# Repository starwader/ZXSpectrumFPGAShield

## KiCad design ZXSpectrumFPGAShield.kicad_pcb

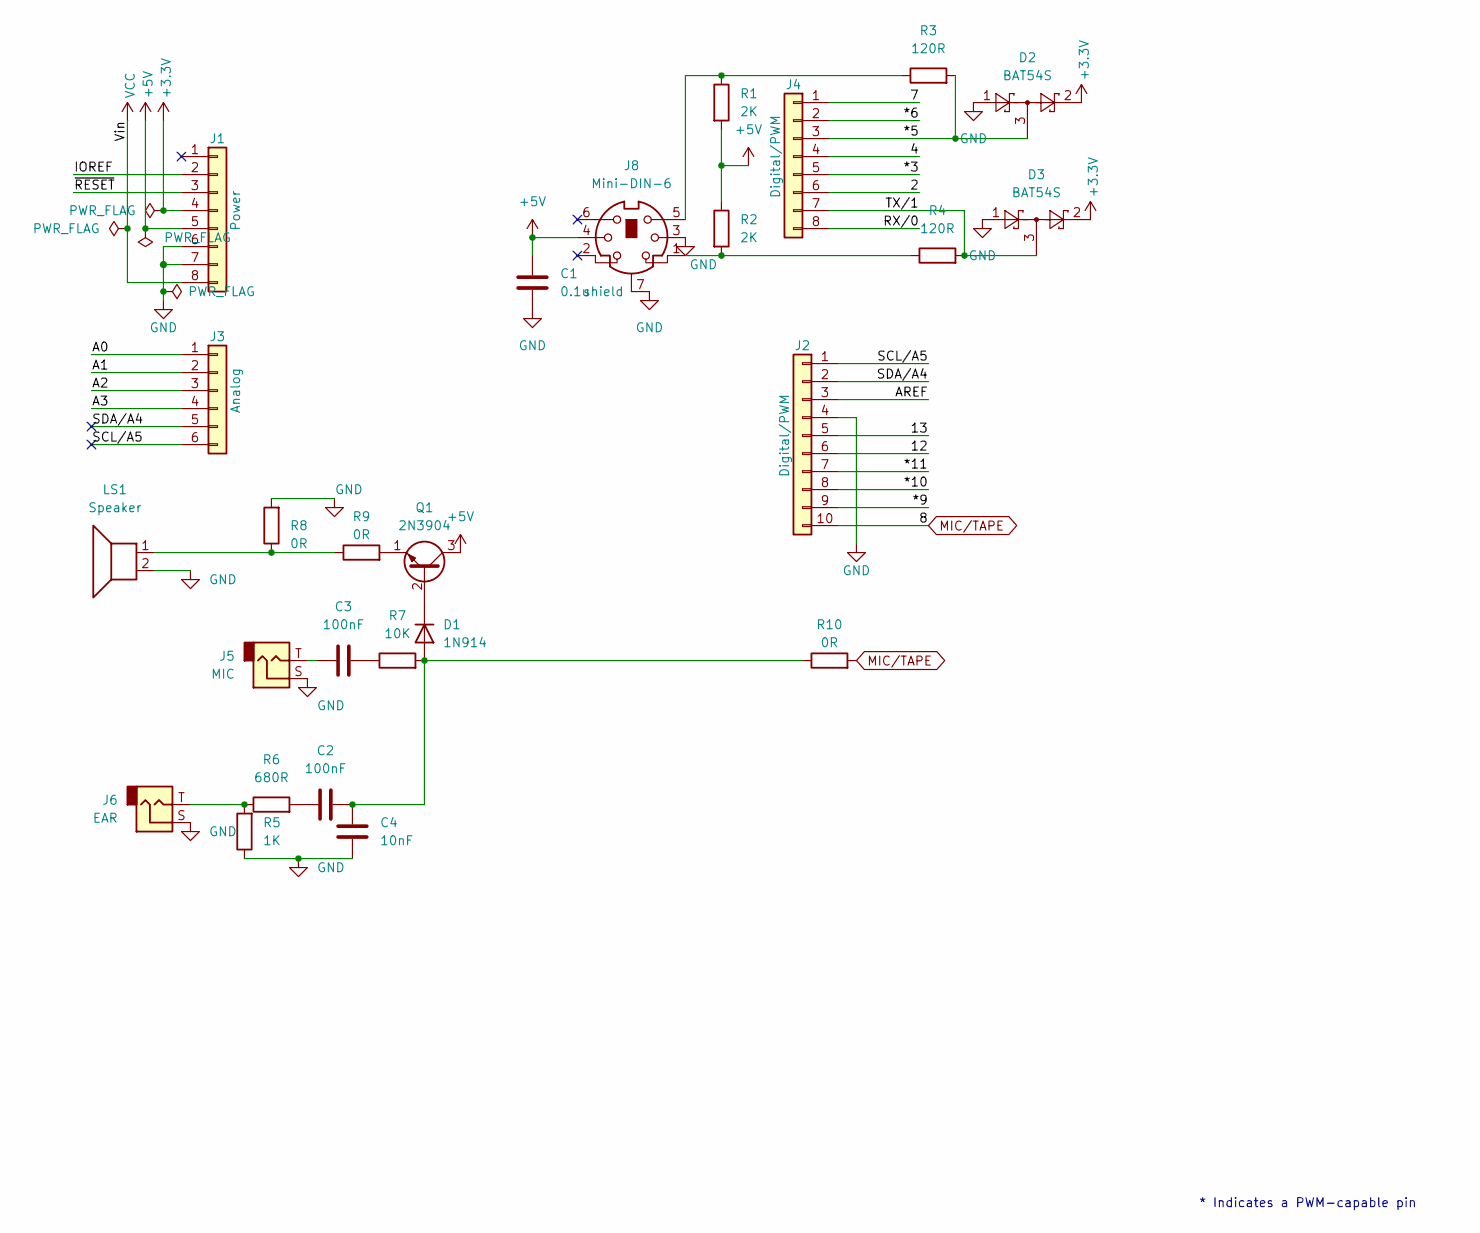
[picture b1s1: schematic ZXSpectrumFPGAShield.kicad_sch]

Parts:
C1: 0.1u; C_Axial_L3.8mm_D2.6mm_P7.50mm_Horizontal
C2, C3: 100nF; C_Rect_L7.0mm_W2.0mm_P5.00mm
C4: 10nF; C_Axial_L3.8mm_D2.6mm_P7.50mm_Horizontal
D1: 1N914; D_DO-35_SOD27_P7.62mm_Horizontal
D2, D3: BAT54S; SOT-23_Handsoldering
J1: Power; PinSocket_1x08_P2.54mm_Vertical
J2: Digital/PWM; PinSocket_1x10_P2.54mm_Vertical
J3: Analog; PinSocket_1x06_P2.54mm_Vertical
J4: Digital/PWM; PinSocket_1x08_P2.54mm_Vertical
J5: MIC; Jack_3.5mm_Lumberg_1503_07_Horizontal
J6: EAR; Jack_3.5mm_Lumberg_1503_07_Horizontal
J8: Mini-DIN-6; Connector_Mini-DIN_Female_6Pin_2rows
LS1: Speaker; Molex_KK-254_AE-6410-02A_1x02_P2.54mm_Vertical
Q1: 2N3904; TO-92_Inline
R1, R2: 2K; R_Axial_DIN0207_L6.3mm_D2.5mm_P7.62mm_Horizontal
R3, R4: 120R; R_Axial_DIN0207_L6.3mm_D2.5mm_P7.62mm_Horizontal
R5: 1K; R_Axial_DIN0207_L6.3mm_D2.5mm_P7.62mm_Horizontal
R6: 680R; R_Axial_DIN0207_L6.3mm_D2.5mm_P7.62mm_Horizontal
R7: 10K; R_Axial_DIN0207_L6.3mm_D2.5mm_P7.62mm_Horizontal
R8, R9, R10: 0R; R_Axial_DIN0207_L6.3mm_D2.5mm_P7.62mm_Horizontal

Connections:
+3V3: D2.2, D3.2, J1.4
+5V: C1.1, J1.5, J8.4, Q1.3 (C), R1.2, R2.1
/2: J4.6
/4: J4.4
/7: J4.1
/12: J2.6
/13: J2.5
/*3: J4.5
/*5: D2.3, J4.3, R3.2
/*6: J4.2
/*9: J2.9
/*10: J2.8
/*11: J2.7
/A0: J3.1
/A1: J3.2
/A2: J3.3
/A3: J3.4
/AREF: J2.3
/IOREF: J1.2
/RX/0: J4.8
/SCL/A5: J2.1, J3.6
/SDA/A4: J2.2, J3.5
/TX/1: D3.3, J4.7, R4.2
/~RESET: J1.3
GND: C1.2, C4.1, D2.1, D3.1, J1.6, J1.7, J2.4, J5.S, J6.S, J8.3, J8.7 (shield), LS1.2, R5.1, R8.2
MIC/TAPE: J2.10, R10.2
unnamed: C2.1, R6.2
unnamed: C2.2, C4.2, D1.2 (A), R7.2, R10.1
unnamed: C3.1, J5.T
unnamed: C3.2, R7.1
unnamed: D1.1 (K), Q1.2 (B)
unnamed: J6.T, R5.2, R6.1
unnamed: J8.1, R2.2, R4.1
unnamed: J8.5, R1.1, R3.1
unnamed: LS1.1, R8.1, R9.1
unnamed: Q1.1 (E), R9.2
VCC: J1.8

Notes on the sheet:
* Indicates a PWM-capable pin

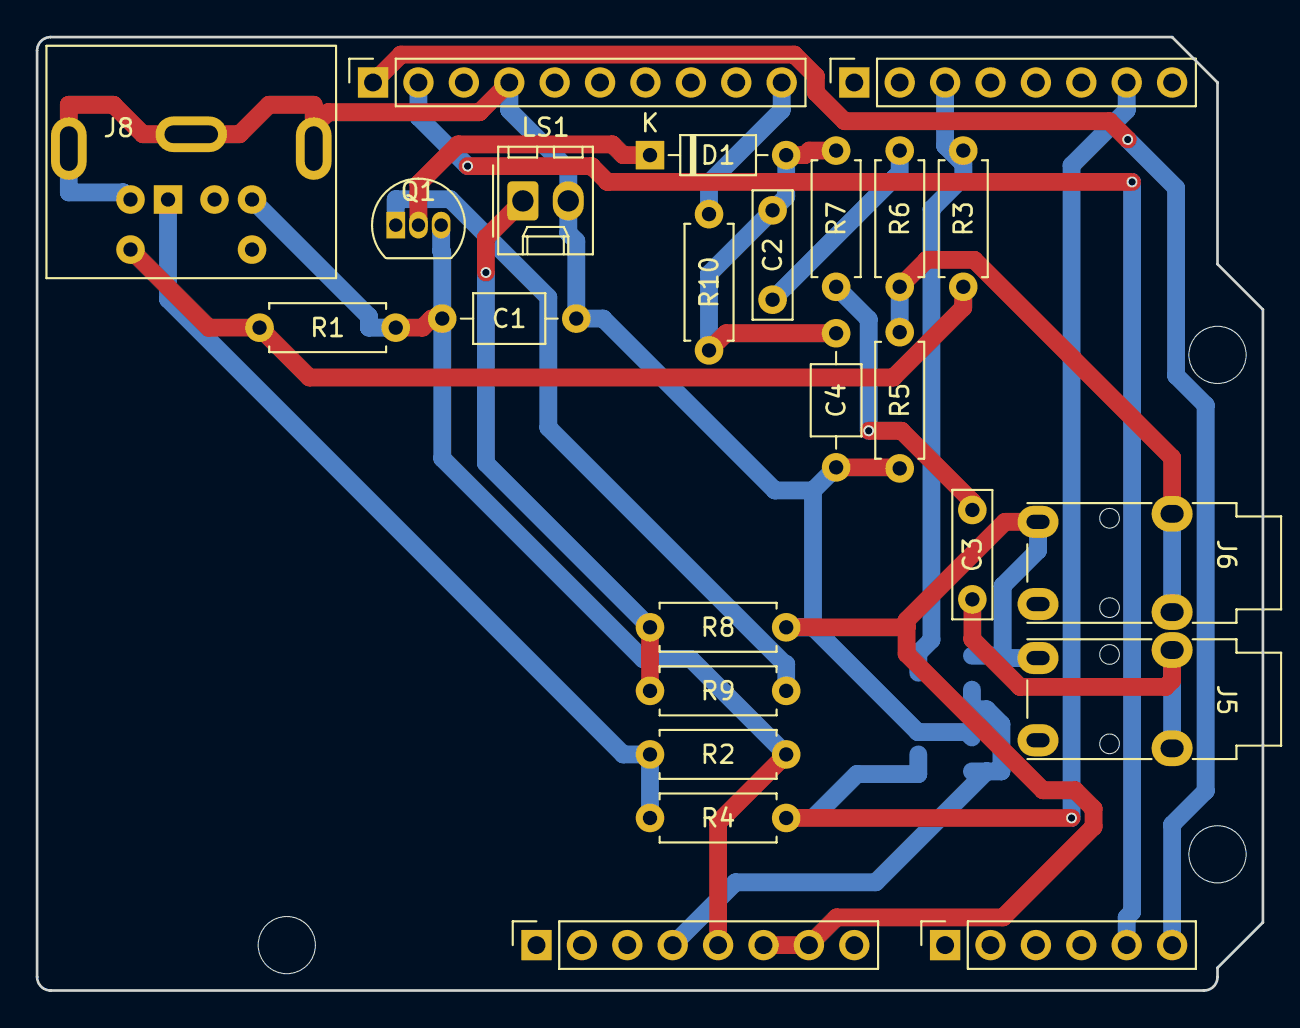
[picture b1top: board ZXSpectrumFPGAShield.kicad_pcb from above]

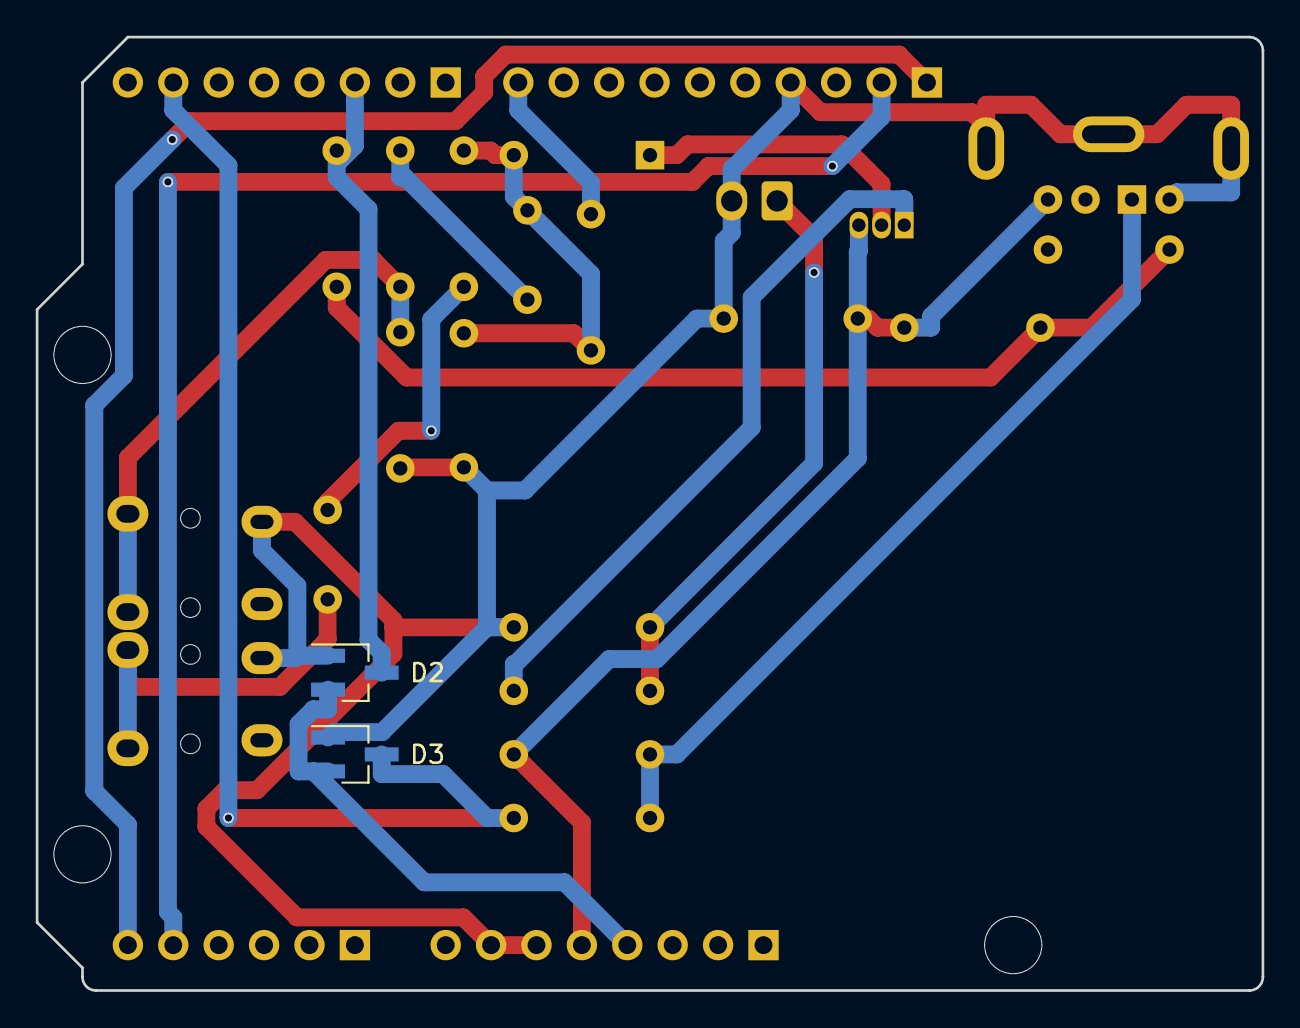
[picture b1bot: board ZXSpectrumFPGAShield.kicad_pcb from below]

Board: 2 copper layers, 68.6 x 53.3 mm, 29 parts (2 on the bottom side), 18 nets.

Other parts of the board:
MH2, MH3, MH4: MountingHole_3.2mm
